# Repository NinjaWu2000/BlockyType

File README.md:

"# BlockyType" 

latest PCB version is V0.3

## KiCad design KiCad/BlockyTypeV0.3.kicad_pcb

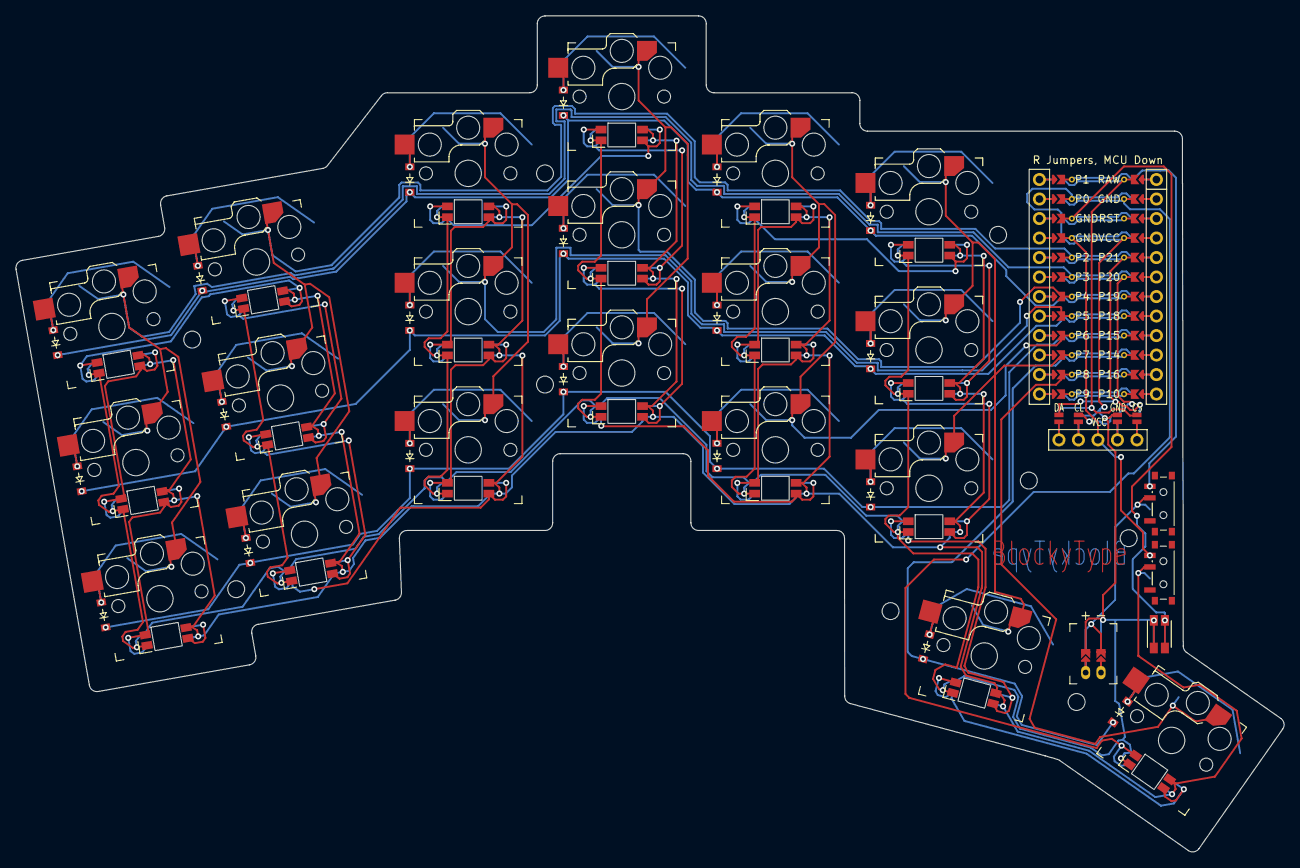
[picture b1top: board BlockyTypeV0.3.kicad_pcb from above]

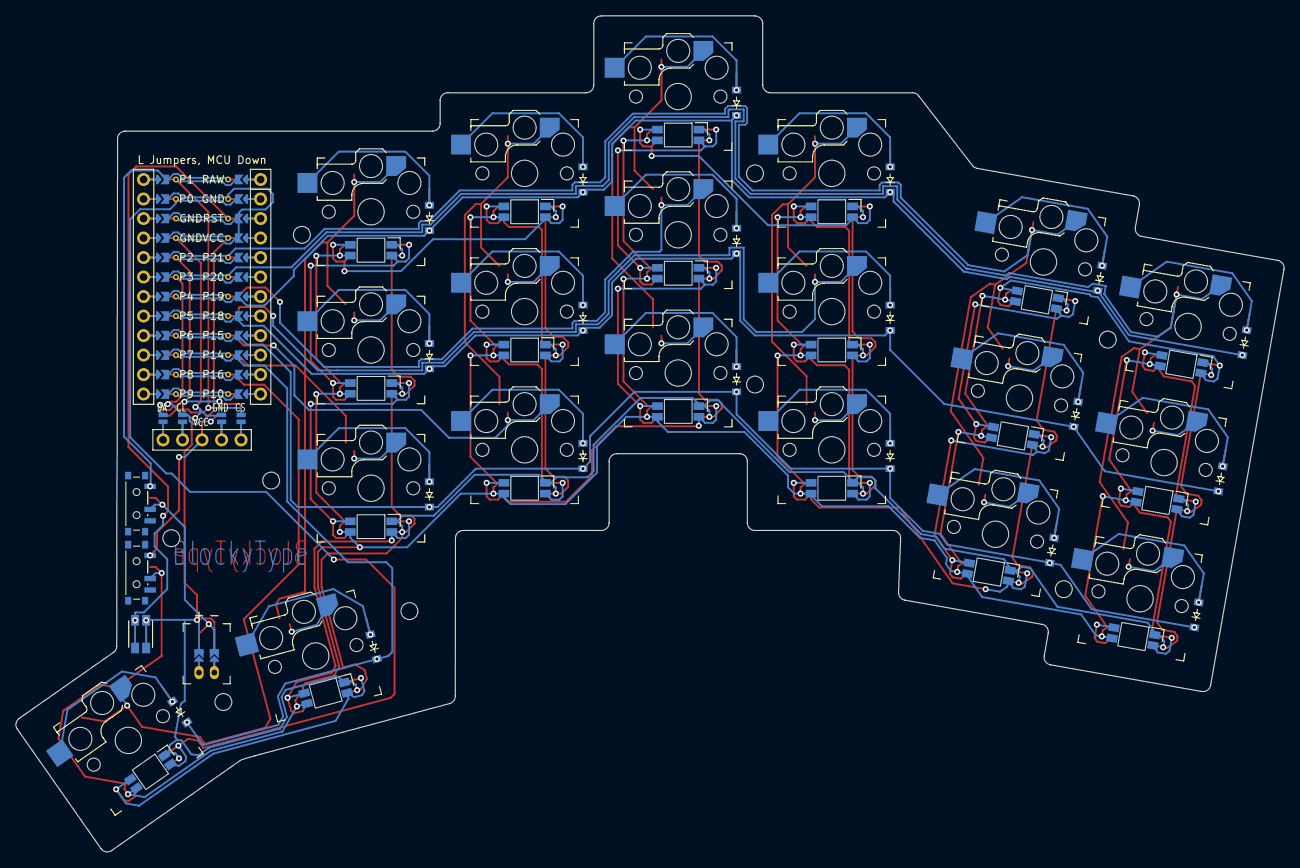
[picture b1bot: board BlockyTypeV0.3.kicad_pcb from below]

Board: 2 copper layers, 165.1 x 108.9 mm, 75 parts (20 on the bottom side), 66 nets.

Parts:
D1, D2, D3, D4, D5, D6, D7, D8, D9, D10, D11, D12, D13, D14, D15, D16, D17, D18, D19, D20: ComboDiode
DISP1: nice!view
JST1: battery_connector_jst_ph_2
LED1, LED2, LED3, LED4, LED5, LED6, LED7, LED8, LED9, LED10, LED11, LED12, LED13, LED14, LED15, LED16, LED17, LED18, LED19, LED20: led_SK6812mini-e (per-key, reversible)
MCU1: mcu_nice_nano
MH1, MH2, MH3, MH4, MH5, MH6, MH7, MH8, MH9: mounting_hole_npth
S1, S2, S3, S4, S5, S6, S7, S8, S9, S10, S11, S12, S13, S14, S15, S16, S17, S18, S19, S20: PG1350
SW1, SW3: power_switch
SW2: sw_reset_side

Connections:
BAT_P: JST1.1, SW3.2, SW3.5
DISP1_1: DISP1.1, DISP1.10, DISP1.23
DISP1_2: DISP1.2, DISP1.11, DISP1.22
DISP1_4: DISP1.4, DISP1.12, DISP1.21
DISP1_5: DISP1.5, DISP1.13, DISP1.20
GND: DISP1.16, DISP1.26, JST1.2, LED1.3, LED2.3, LED3.3, LED4.3, LED5.3, LED6.3, LED7.3, LED8.3, LED9.3, LED10.3, LED11.3, LED12.3, LED13.3, LED14.3, LED15.3, LED16.3, LED17.3, LED18.3, LED19.3, LED20.3, MCU1.103, MCU1.104, MCU1.123, SW2.1
JST1_1: JST1.11, JST1.21, JST1.31
JST1_2: JST1.12, JST1.22, JST1.32
P0: LED20.4, MCU1.102
P1: DISP1.17, DISP1.27, MCU1.101
P2: DISP1.14, DISP1.24, MCU1.105
P3: DISP1.15, DISP1.25, MCU1.106
P4: D3.1, D6.1, D9.1, D12.1, D15.1, D18.1, MCU1.107
P5: D2.1, D5.1, D8.1, D11.1, D14.1, D17.1, MCU1.108
P6: D1.1, D4.1, D7.1, D10.1, D13.1, D16.1, MCU1.109
P7: D19.1, D20.1, MCU1.110
P14: MCU1.115, S16.1, S17.1, S18.1, S19.1
P15: MCU1.116, S13.1, S14.1, S15.1
P16: MCU1.114, S20.1
P18: MCU1.117, S7.1, S8.1, S9.1
P19: MCU1.118, S10.1, S11.1, S12.1
P20: MCU1.119, S1.1, S2.1, S3.1
P21: MCU1.120, S4.1, S5.1, S6.1
RAW: MCU1.124, SW3.3, SW3.6
RST: MCU1.122, SW2.2
VCC: DISP1.3, MCU1.121, SW1.3, SW1.6
VCC_LED: LED1.1, LED2.1, LED3.1, LED4.1, LED5.1, LED6.1, LED7.1, LED8.1, LED9.1, LED10.1, LED11.1, LED12.1, LED13.1, LED14.1, LED15.1, LED16.1, LED17.1, LED18.1, LED19.1, LED20.1, SW1.2, SW1.5
home_home: D19.2, S19.2
index_down: D13.2, S13.2
index_home: D14.2, S14.2
index_up: D15.2, S15.2
inner_down: D16.2, S16.2
inner_home: D17.2, S17.2
inner_up: D18.2, S18.2
innermost_home: D20.2, S20.2
led_2: LED19.4, LED20.2
led_3: LED16.4, LED19.2
led_4: LED16.2, LED17.4
led_5: LED17.2, LED18.4
led_6: LED15.4, LED18.2
led_7: LED14.4, LED15.2
led_8: LED13.4, LED14.2
led_9: LED10.4, LED13.2
led_10: LED10.2, LED11.4
led_11: LED11.2, LED12.4
led_12: LED9.4, LED12.2
led_13: LED8.4, LED9.2
led_14: LED7.4, LED8.2
led_15: LED4.4, LED7.2
led_16: LED4.2, LED5.4
led_17: LED5.2, LED6.4
led_18: LED3.4, LED6.2
led_19: LED2.4, LED3.2
led_20: LED1.4, LED2.2
middle_down: D10.2, S10.2
middle_home: D11.2, S11.2
middle_up: D12.2, S12.2
outer_down: D1.2, S1.2
outer_home: D2.2, S2.2
outer_up: D3.2, S3.2
pinky_down: D4.2, S4.2
pinky_home: D5.2, S5.2
pinky_up: D6.2, S6.2
ring_down: D7.2, S7.2
ring_home: D8.2, S8.2
ring_up: D9.2, S9.2

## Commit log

2024-10-12 add files
2024-10-13 generated the gerber files for the pcb
2025-06-15 Add files via upload
    Finished the corrected board with correct LED connections. Not tested for PCB service tolerances.
